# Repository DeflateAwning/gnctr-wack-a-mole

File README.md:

# gnctr-wack-a-mole
A quick PCB and firmware for a Wack-a-Mole game for the 2023 GNCTR Tech Ex

## Dev Notes
* Display Library: https://github.com/avishorp/TM1637/blob/master/TM1637Display.h
    * 7seg Segment IDs: https://github.com/avishorp/TM1637/issues/94

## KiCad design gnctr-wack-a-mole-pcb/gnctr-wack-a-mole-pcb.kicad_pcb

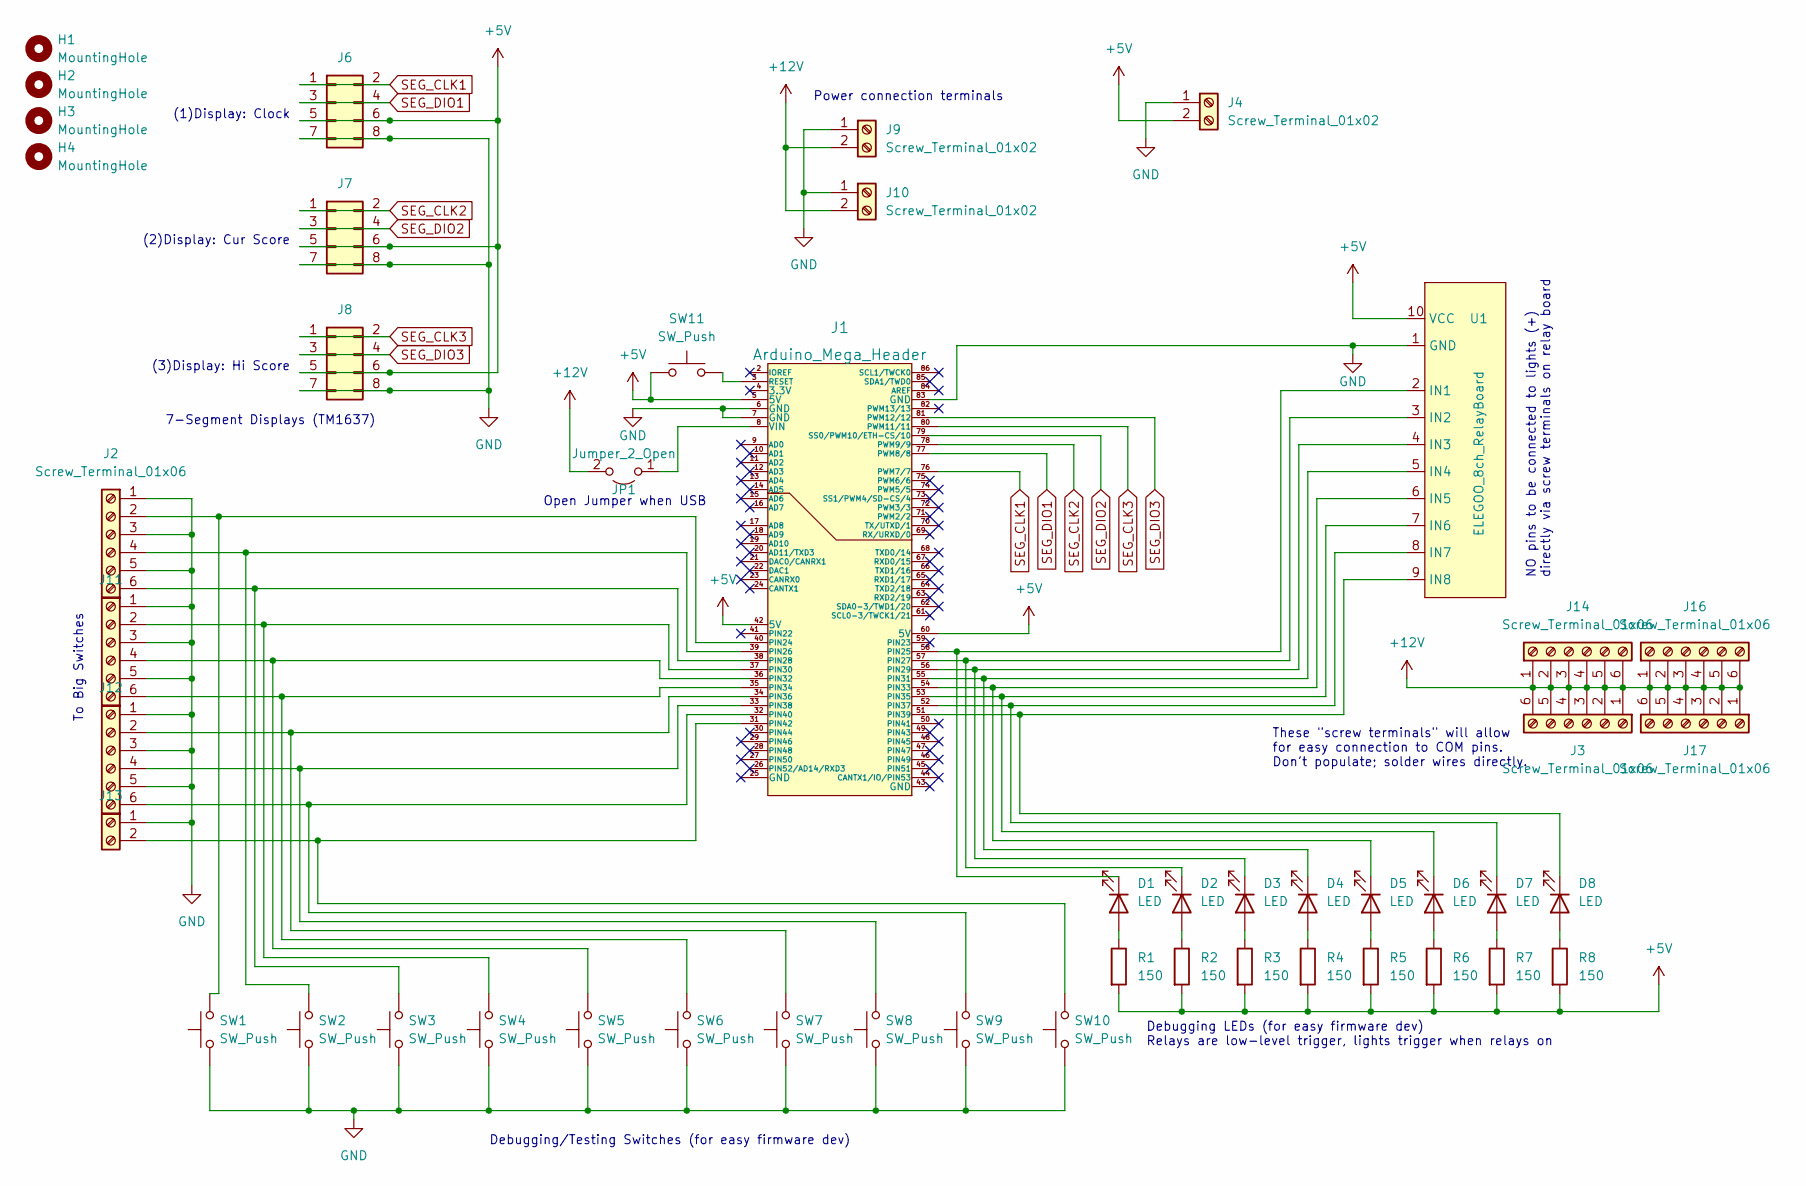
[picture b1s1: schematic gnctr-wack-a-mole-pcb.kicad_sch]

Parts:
D1, D2, D3, D4, D5, D6, D7, D8: LED; LED_1206_3216Metric_Pad1.42x1.75mm_HandSolder
H1, H2, H3, H4: MountingHole; MountingHole_4mm
J1: Arduino_Mega_Header; arduino_mega_header
J2, J3, J11, J12, J14, J16, J17: Screw_Terminal_01x06; TerminalBlock_bornier-6_P5.08mm
J4, J9, J10, J13: Screw_Terminal_01x02; TerminalBlock_bornier-2_P5.08mm
J6, J7, J8: Conn_02x04_Row_Letter_Last; PinHeader_2x04_P2.54mm_Vertical
JP1: Jumper_2_Open; PinHeader_1x02_P2.54mm_Vertical
R1, R2, R3, R4, R5, R6, R7, R8: 150; R_1206_3216Metric_Pad1.30x1.75mm_HandSolder
SW1, SW2, SW3, SW4, SW5, SW6, SW7, SW8, SW9, SW10, SW11: SW_Push; SW_PUSH_6mm
U1: ELEGOO_8ch_RelayBoard; elegoo_8ch_relay

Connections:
+5V: J1.5 (5V), J1.42 (5V), J1.60 (5V), J4.2, J6.5, J6.6, J7.5, J7.6, J8.5, J8.6, R1.2, R2.2, R3.2, R4.2, R5.2, R6.2, R7.2, R8.2, SW11.1, U1.10 (VCC)
+12V: J3.1, J3.2, J3.3, J3.4, J3.5, J3.6, J9.2, J10.2, J14.1, J14.2, J14.3, J14.4, J14.5, J14.6, J16.1, J16.2, J16.3, J16.4, J16.5, J16.6, J17.1, J17.2, J17.3, J17.4, J17.5, J17.6, JP1.2 (B)
GND: J1.6 (GND), J1.7 (GND), J1.83 (GND), J2.1, J2.3, J2.5, J4.1, J6.7, J6.8, J7.7, J7.8, J8.7, J8.8, J9.1, J10.1, J11.1, J11.3, J11.5, J12.1, J12.3, J12.5, J13.1, SW1.1, SW2.1, SW3.1, SW4.1, SW5.1, SW6.1, SW7.1, SW8.1, SW9.1, SW10.1, U1.1 (GND)
unnamed: J1.3 (RESET), SW11.2
unnamed: J1.8 (VIN), JP1.1 (A)
unnamed: J1.31 (PIN42), J13.2, SW10.2
unnamed: J1.32 (PIN40), J12.6, SW9.2
unnamed: J1.36 (PIN32), J11.4, SW5.2
unnamed: J1.37 (PIN30), J11.2, SW4.2
unnamed: J1.38 (PIN28), J2.6, SW3.2
unnamed: J1.39 (PIN26), J2.4, SW2.2
unnamed: D8.1 (K), J1.51 (PIN39), U1.9 (IN8)
unnamed: D7.1 (K), J1.52 (PIN37), U1.8 (IN7)
unnamed: D6.1 (K), J1.53 (PIN35), U1.7 (IN6)
unnamed: D5.1 (K), J1.54 (PIN33), U1.6 (IN5)
unnamed: D4.1 (K), J1.55 (PIN31), U1.5 (IN4)
unnamed: D3.1 (K), J1.56 (PIN29), U1.4 (IN3)
unnamed: D2.1 (K), J1.57 (PIN27), U1.3 (IN2)
unnamed: D1.1 (K), J1.58 (PIN25), U1.2 (IN1)
unnamed: D1.2 (A), R1.1
unnamed: D2.2 (A), R2.1
unnamed: D3.2 (A), R3.1
unnamed: D4.2 (A), R4.1
unnamed: D5.2 (A), R5.1
unnamed: D6.2 (A), R6.1
unnamed: D7.2 (A), R7.1
unnamed: D8.2 (A), R8.1
unnamed: J1.40 (PIN24), J2.2, SW1.2
unnamed: J1.35 (PIN34), J11.6, SW6.2
unnamed: J1.34 (PIN36), J12.2, SW7.2
unnamed: J1.33 (PIN38), J12.4, SW8.2
SEG_CLK1: J1.76 (PWM7/7), J6.1, J6.2
SEG_CLK2: J1.78 (PWM9/9), J7.1, J7.2
SEG_CLK3: J1.80 (PWM11/11), J8.1, J8.2
SEG_DIO1: J1.77 (PWM8/8), J6.3, J6.4
SEG_DIO2: J1.79 (SS0/PWM10/ETH-CS/10), J7.3, J7.4
SEG_DIO3: J1.81 (PWM12/12), J8.3, J8.4

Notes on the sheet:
Debugging LEDs (for easy firmware dev) Relays are low-level trigger, lights trigger when relays on
Power connection terminals
To Big Switches
7-Segment Displays (TM1637)
NO pins to be connected to lights (+) directly via screw terminals on relay board
Open Jumper when USB
(2)Display: Cur Score
Debugging/Testing Switches (for easy firmware dev)
These "screw terminals" will allow for easy connection to COM pins. Don't populate; solder wires directly.
(3)Display: Hi Score
(1)Display: Clock

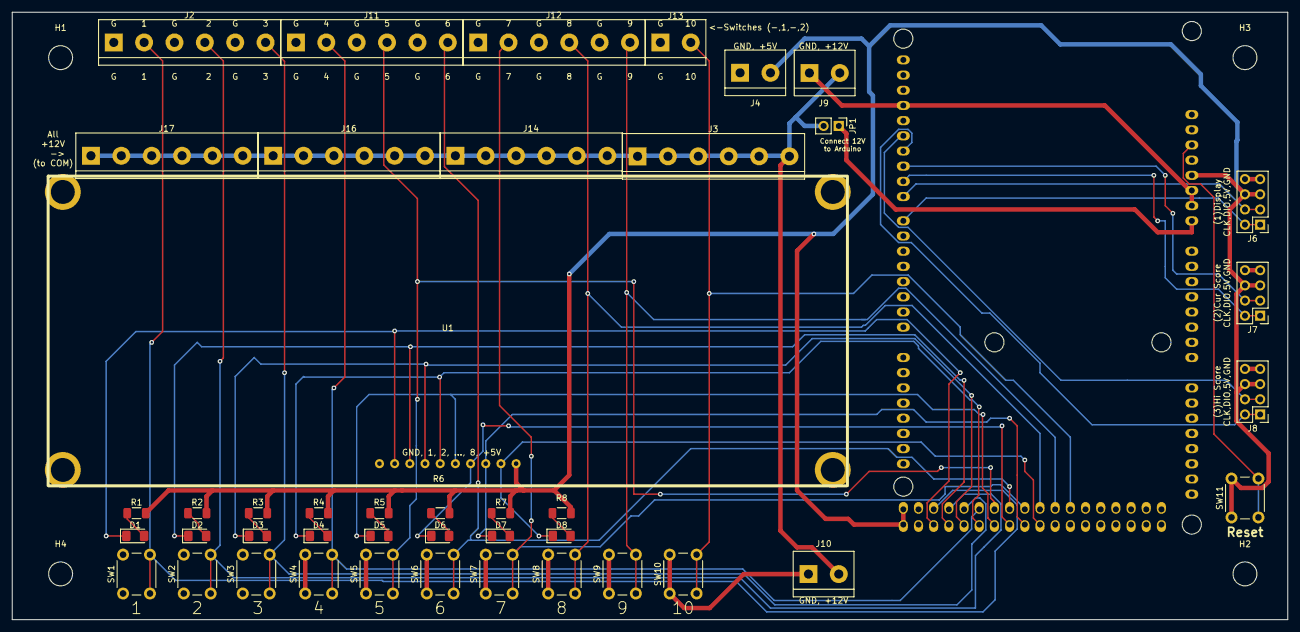
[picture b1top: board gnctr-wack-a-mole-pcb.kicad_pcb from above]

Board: 2 copper layers, 213.4 x 101.6 mm, 48 parts (1 on the bottom side), 37 nets.

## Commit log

2022-11-12 Add ordered PCB design v1
2022-11-12 Update gitignore from github's current online gitignore repo
2022-11-18 Update schematic, add testing firmware
2022-11-22 Add 7-seg testing code and notes
2022-11-22 Integrate tutorial code with testing framework
2022-11-29 Fix high current draw relay testing issue
2022-12-14 EEPROMhigh score, better high score behaviour
2022-12-21 Add press to start and custom text
2023-01-21 Minor value changes, add inactive timeout
2023-01-21 Improve done message, add exit from test sequence
2023-01-21 Add countdown timer
2024-01-04 Fix KiCAD gitignore
